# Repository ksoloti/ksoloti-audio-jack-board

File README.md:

# ksoloti-audio-jack-board 

Five 6.35mm audio jacks with headers to interface with the Ksoloti Core's line i/o header and headphones header.

- Two mono line input jacks
- Two mono line output jacks
- One stereo headphones jack

Board dimensions: 100mm * 34mm
Jacks used: NRJ6HF
These are actually stereo jacks, but on the line i/o the ring terminals are not connected to anything. You could rewire them to get stereo line i/o or anything else.

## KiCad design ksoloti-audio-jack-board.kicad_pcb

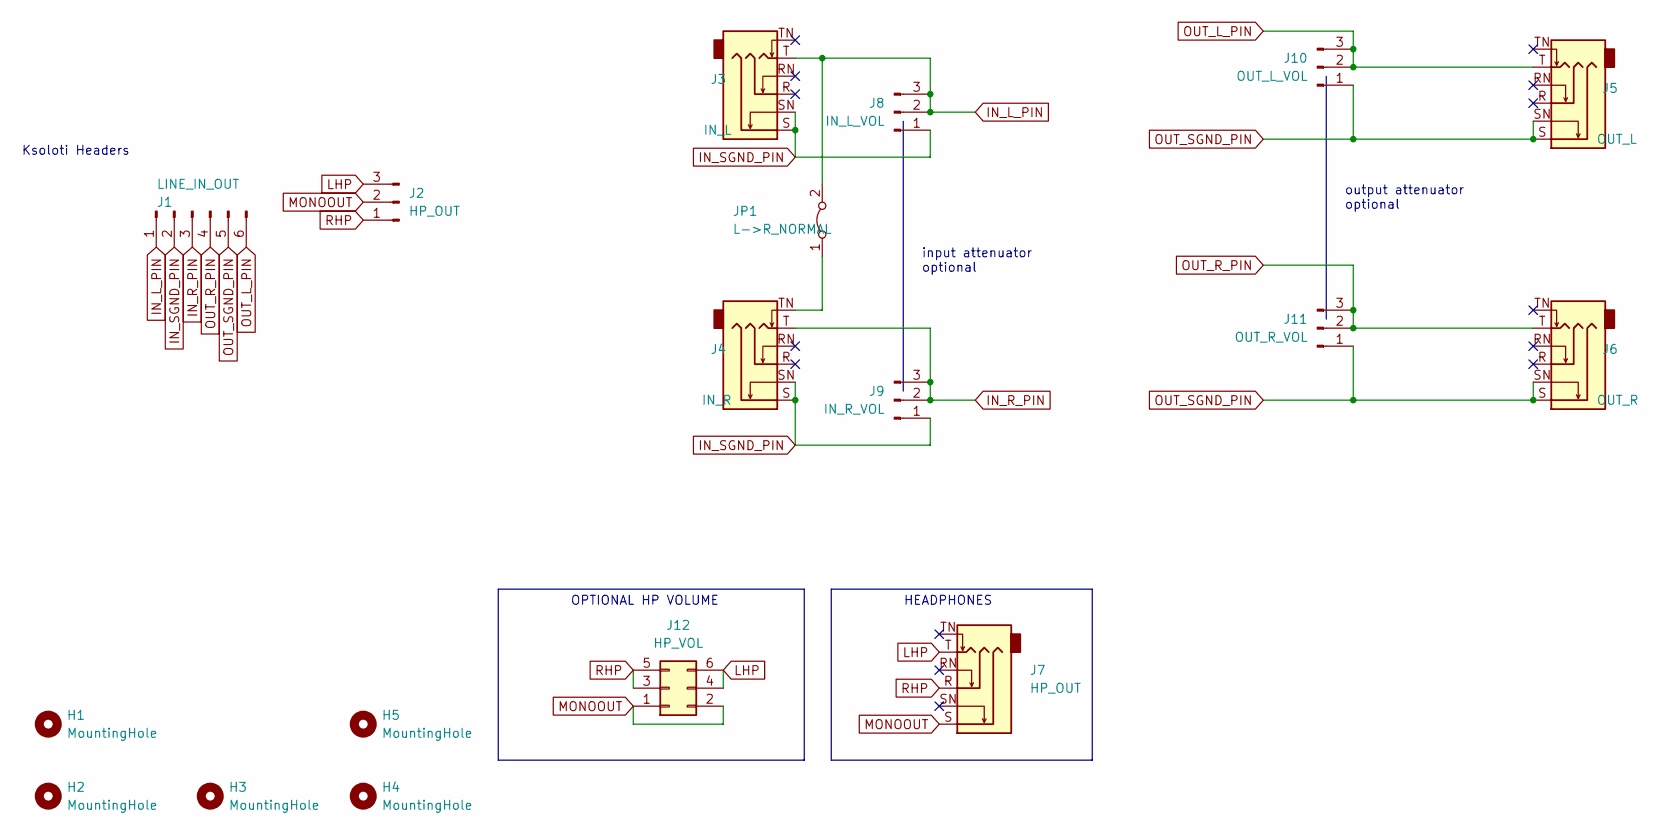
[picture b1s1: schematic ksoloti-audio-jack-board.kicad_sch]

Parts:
H1, H2, H3, H4, H5: MountingHole; MountingHole_3.2mm_M3_Pad_noVia_tight
J1: LINE_IN_OUT; PinHeader_1x06_P2.54mm_Vertical
J2: HP_OUT; PinHeader_1x03_P2.54mm_Vertical
J3: IN_L; Jack_6.35mm_Neutrik_NRJ6HF_Horizontal_no_screwhole
J4: IN_R; Jack_6.35mm_Neutrik_NRJ6HF_Horizontal_no_screwhole
J5: OUT_L; Jack_6.35mm_Neutrik_NRJ6HF_Horizontal_no_screwhole
J6: OUT_R; Jack_6.35mm_Neutrik_NRJ6HF_Horizontal_no_screwhole
J7: HP_OUT; Jack_6.35mm_Neutrik_NRJ6HF_Horizontal_no_screwhole
J8: IN_L_VOL; PinHeader_1x03_P2.54mm_Vertical
J9: IN_R_VOL; PinHeader_1x03_P2.54mm_Vertical
J10: OUT_L_VOL; PinHeader_1x03_P2.54mm_Vertical
J11: OUT_R_VOL; PinHeader_1x03_P2.54mm_Vertical
J12: HP_VOL; PinHeader_2x03_P2.54mm_Vertical
JP1: L->R_NORMAL; SolderJumper-2_0603_Bridged_0_25mm

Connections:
IN_L_PIN: J1.1, J3.T, J8.2, J8.3, JP1.2 (B)
IN_R_PIN: J1.3, J4.T, J9.2, J9.3
IN_SGND_PIN: J1.2, J3.S, J3.SN, J4.S, J4.SN, J8.1, J9.1
LHP: J2.3, J7.T, J12.4, J12.6
MONOOUT: J2.2, J7.S, J12.1, J12.2
unnamed: J4.TN, JP1.1 (A)
OUT_L_PIN: J1.6, J5.T, J10.2, J10.3
OUT_R_PIN: J1.4, J6.T, J11.2, J11.3
OUT_SGND_PIN: J1.5, J5.S, J5.SN, J6.S, J6.SN, J10.1, J11.1
RHP: J2.1, J7.R, J12.3, J12.5

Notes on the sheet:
OPTIONAL HP VOLUME
HEADPHONES
Ksoloti Headers
input attenuator optional
output attenuator optional

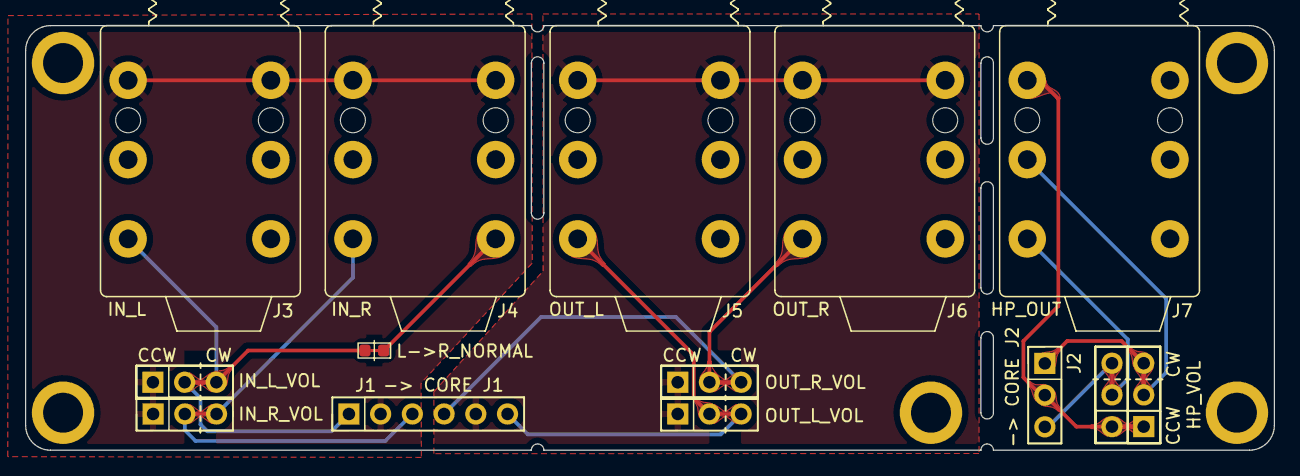
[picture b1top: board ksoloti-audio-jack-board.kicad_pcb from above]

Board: 2 copper layers, 100.0 x 34.0 mm, 18 parts (0 on the bottom side), 10 nets.

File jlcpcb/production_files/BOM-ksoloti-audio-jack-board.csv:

Comment,Designator,Footprint,LCSC
OUT_R_VOL,J11,PinHeader_1x03_P2.54mm_Vertical,
MountingHole,H5,MountingHole_3.2mm_M3_Pad_noVia_tight,
MountingHole,H1,MountingHole_3.2mm_M3_Pad_noVia_tight,
IN_L,J3,Jack_6.35mm_Neutrik_NRJ6HF_Horizontal_no_screwhole,
IN_R_VOL,J9,PinHeader_1x03_P2.54mm_Vertical,
MountingHole,H2,MountingHole_3.2mm_M3_Pad_noVia_tight,
OUT_L,J5,Jack_6.35mm_Neutrik_NRJ6HF_Horizontal_no_screwhole,
IN_L_VOL,J8,PinHeader_1x03_P2.54mm_Vertical,
HP_OUT,J7,Jack_6.35mm_Neutrik_NRJ6HF_Horizontal_no_screwhole,
LINE_IN_OUT,J1,PinHeader_1x06_P2.54mm_Vertical,
OUT_L_VOL,J10,PinHeader_1x03_P2.54mm_Vertical,
MountingHole,H4,MountingHole_3.2mm_M3_Pad_noVia_tight,
IN_R,J4,Jack_6.35mm_Neutrik_NRJ6HF_Horizontal_no_screwhole,
MountingHole,H3,MountingHole_3.2mm_M3_Pad_noVia_tight,
L->R_NORMAL,JP1,SolderJumper-2_0603_Bridged_0_25mm,
HP_VOL,J12,PinHeader_2x03_P2.54mm_Vertical,
HP_OUT,J2,PinHeader_1x03_P2.54mm_Vertical,
OUT_R,J6,Jack_6.35mm_Neutrik_NRJ6HF_Horizontal_no_screwhole,

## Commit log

2024-03-12 update footprints, keep out zone around jumper
2024-03-20 update project (board dimensions now 100m*34mm)
2024-03-20 add jlc gerber files
2024-03-20 add images to readme
2024-03-20 edit
2024-05-29 ignore fp-info-cache
